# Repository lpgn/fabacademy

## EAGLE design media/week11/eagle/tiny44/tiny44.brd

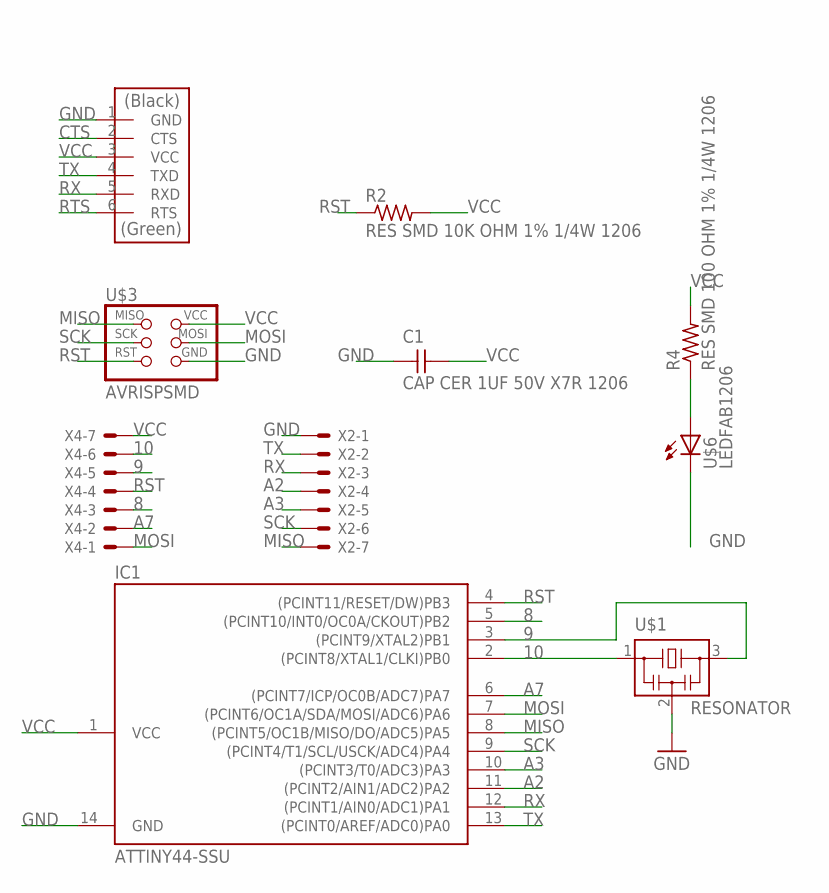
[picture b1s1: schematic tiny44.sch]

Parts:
C1: CAP CER 1UF 50V X7R 1206; C1206FAB
IC1: ATTINY44-SSU; SOIC14
R2: RES SMD 10K OHM 1% 1/4W 1206; R1206FAB
R4: RES SMD 100 OHM 1% 1/4W 1206; R1206FAB
U$1: RESONATOR; EFOBM; MPN AWSCR-20.00MTD-T
U$2: FTDI-SMD-HEADER; 1X06SMD
U$3: AVRISPSMD; 2X03SMD
U$6: LEDFAB1206; LED1206FAB
X2, X4: KK-156-7

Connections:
8: IC1.5 ((PCINT10/INT0/OC0A/CKOUT)PB2), X4.3
9: IC1.3 ((PCINT9/XTAL2)PB1), U$1.3, X4.5
10: IC1.2 ((PCINT8/XTAL1/CLKI)PB0), U$1.1, X4.6
A2: IC1.11 ((PCINT2/AIN1/ADC2)PA2), X2.4
A3: IC1.10 ((PCINT3/T0/ADC3)PA3), X2.5
A7: IC1.6 ((PCINT7/ICP/OC0B/ADC7)PA7), X4.2
CTS: U$2.2 (CTS)
GND: C1.1, IC1.14 (GND), U$1.2, U$2.1 (GND), U$3.6 (GND), U$6.2 (C), X2.1
MISO: IC1.8 ((PCINT5/OC1B/MISO/DO/ADC5)PA5), U$3.1 (MISO), X2.7
MOSI: IC1.7 ((PCINT6/OC1A/SDA/MOSI/ADC6)PA6), U$3.4 (MOSI), X4.1
PB2: R4.1, U$6.1 (A)
RST: IC1.4 ((PCINT11/RESET/DW)PB3), R2.1, U$3.5 (RST), X4.4
RTS: U$2.6 (RTS)
RX: IC1.12 ((PCINT1/AIN0/ADC1)PA1), U$2.5 (RXD), X2.3
SCK: IC1.9 ((PCINT4/T1/SCL/USCK/ADC4)PA4), U$3.3 (SCK), X2.6
TX: IC1.13 ((PCINT0/AREF/ADC0)PA0), U$2.4 (TXD), X2.2
VCC: C1.2, IC1.1 (VCC), R2.2, R4.2, U$2.3 (VCC), U$3.2 (VCC), X4.7

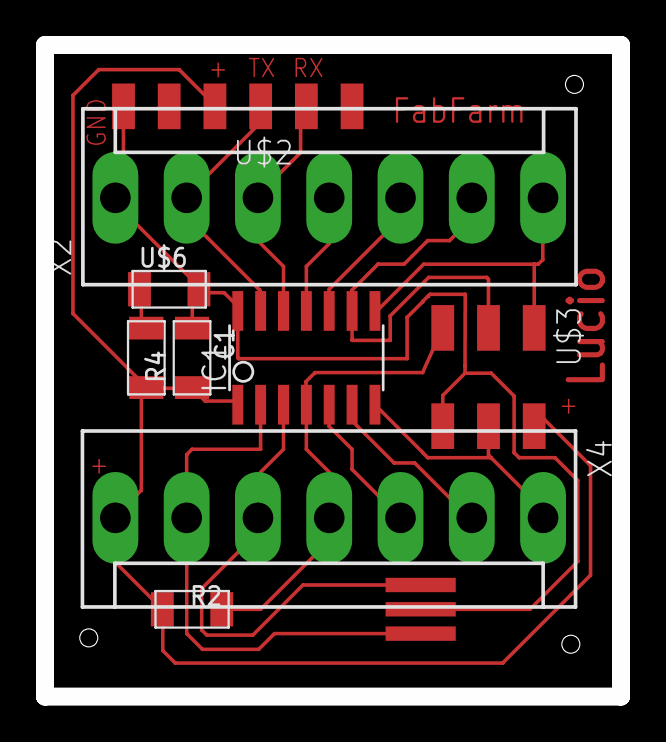
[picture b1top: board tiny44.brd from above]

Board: 2 copper layers, 32.0 x 36.2 mm, 10 parts (0 on the bottom side), 15 nets.

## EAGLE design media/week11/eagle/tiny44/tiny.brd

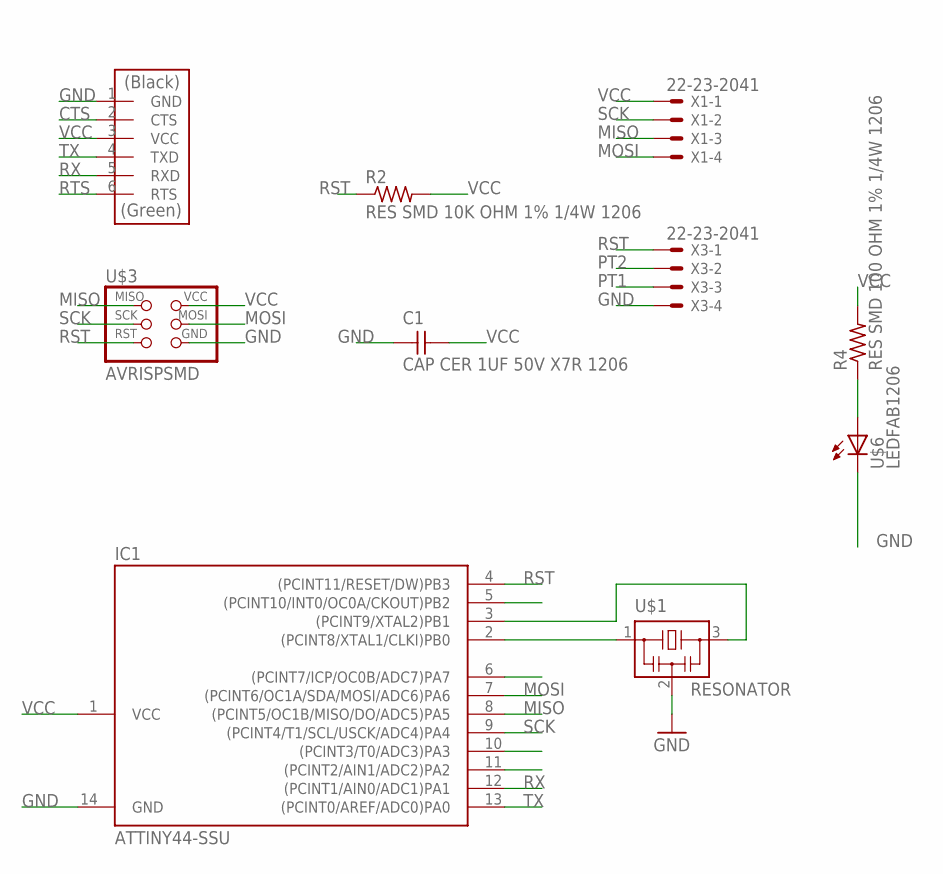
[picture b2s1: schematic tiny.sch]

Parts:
C1: CAP CER 1UF 50V X7R 1206; C1206FAB
IC1: ATTINY44-SSU; SOIC14
R2: RES SMD 10K OHM 1% 1/4W 1206; R1206FAB
R4: RES SMD 100 OHM 1% 1/4W 1206; R1206FAB
U$1: RESONATOR; EFOBM; MPN AWSCR-20.00MTD-T
U$2: FTDI-SMD-HEADER; 1X06SMD
U$3: AVRISPSMD; 2X03SMD
U$6: LEDFAB1206; LED1206FAB
X1, X3: 22-23-2041

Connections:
CTS: U$2.2 (CTS)
GND: C1.1, IC1.14 (GND), U$1.2, U$2.1 (GND), U$3.6 (GND), U$6.2 (C), X3.4
MISO: IC1.8 ((PCINT5/OC1B/MISO/DO/ADC5)PA5), U$3.1 (MISO), X1.3
MOSI: IC1.7 ((PCINT6/OC1A/SDA/MOSI/ADC6)PA6), U$3.4 (MOSI), X1.4
unnamed: IC1.3 ((PCINT9/XTAL2)PB1), U$1.3
unnamed: IC1.2 ((PCINT8/XTAL1/CLKI)PB0), U$1.1
PB2: R4.1, U$6.1 (A)
PT1: X3.3
PT2: X3.2
RST: IC1.4 ((PCINT11/RESET/DW)PB3), R2.1, U$3.5 (RST), X3.1
RTS: U$2.6 (RTS)
RX: IC1.12 ((PCINT1/AIN0/ADC1)PA1), U$2.5 (RXD)
SCK: IC1.9 ((PCINT4/T1/SCL/USCK/ADC4)PA4), U$3.3 (SCK), X1.2
TX: IC1.13 ((PCINT0/AREF/ADC0)PA0), U$2.4 (TXD)
VCC: C1.2, IC1.1 (VCC), R2.2, R4.2, U$2.3 (VCC), U$3.2 (VCC), X1.1

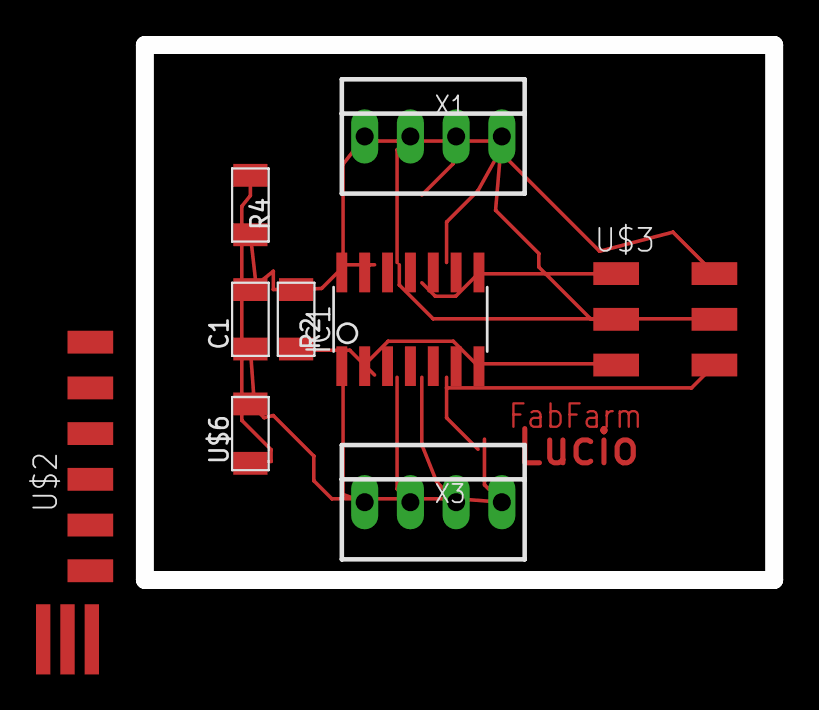
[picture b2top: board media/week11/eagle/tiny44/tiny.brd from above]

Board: 2 copper layers, 35.0 x 29.7 mm, 10 parts (0 on the bottom side), 11 nets.

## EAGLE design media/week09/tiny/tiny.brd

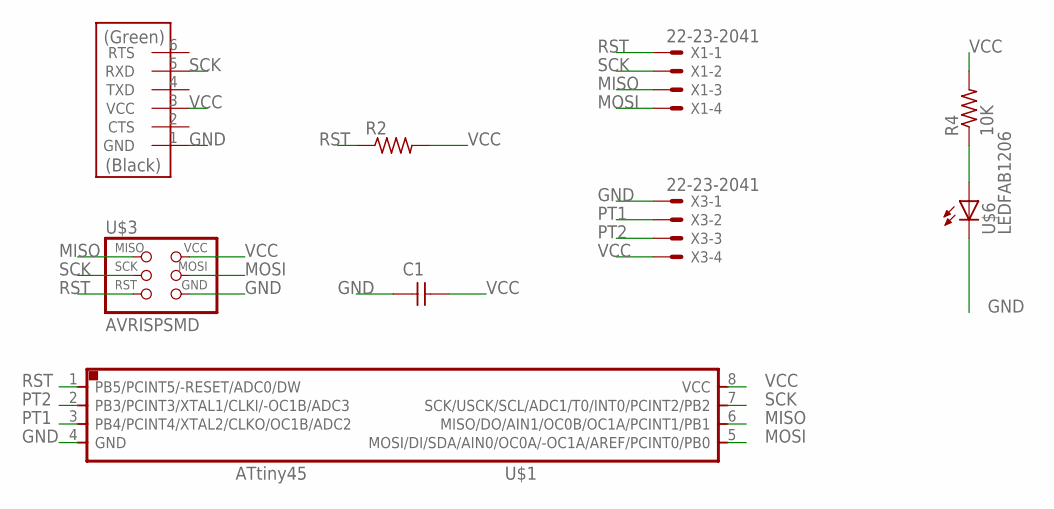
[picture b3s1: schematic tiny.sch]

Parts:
C1: CAP-UNPOLARIZEDFAB; C1206FAB
R2: RES-US1206FAB; R1206FAB
R4: 10K; R1206FAB
U$1: ATTINY45SI; SOIC8
U$3: AVRISPSMD; 2X03SMD
U$4: FTDI-SMD-HEADER; 1X06SMD
U$6: LEDFAB1206; LED1206FAB
X1, X3: 22-23-2041

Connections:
GND: C1.1, U$1.4 (GND), U$3.6 (GND), U$4.1 (GND), U$6.2 (C), X3.1
MISO: U$1.6 (MISO/DO/AIN1/OC0B/OC1A/PCINT1/PB1), U$3.1 (MISO), X1.3
MOSI: U$1.5 (MOSI/DI/SDA/AIN0/OC0A/-OC1A/AREF/PCINT0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), U$3.4 (MOSI), X1.4
PB2: R4.1, U$6.1 (A)
PT1: U$1.3 (PB4/PCINT4/XTAL2/CLKO/OC1B/ADC2), X3.2
PT2: U$1.2 (PB3/PCINT3/XTAL1/CLKI/-OC1B/ADC3), X3.3
RST: R2.1, U$1.1 (PB5/PCINT5/-RESET/ADC0/DW), U$3.5 (RST), X1.1
SCK: U$1.7 (SCK/USCK/SCL/ADC1/T0/INT0/PCINT2/PB2), U$3.3 (SCK), U$4.5 (RXD), X1.2
VCC: C1.2, R2.2, R4.2, U$1.8 (VCC), U$3.2 (VCC), U$4.3 (VCC), X3.4

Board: 2 copper layers, 9 parts (0 on the bottom side), 9 nets, no tracks yet.

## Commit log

2018-02-26 Add new file
2018-02-26 Initial commit after migration to new git repo
2018-02-27 Week 6 first part
2018-02-27 html was not saved before now it is
2018-02-28 week6
2018-02-28 small fix
2018-02-28 english language error correction
2018-03-06 updates for week 7
2020-02-01 adaptations to 2020
2020-02-10 week2 images and other changes
2020-02-10 spell check
2020-02-10 spell check2
2020-02-12 week3 media
2020-02-19 week4 media
2020-02-26 adding media for week5
2020-02-26 adding gcode
2020-02-26 adding video
2020-02-26 adding stl file
2020-02-26 adding another stl file
2020-02-26 yet anothert stl
2020-03-03 week5 details
2020-03-04 week5 added pic
2020-03-04 week5 text change
2020-03-04 week6 media
2020-03-11 week8 media
2020-04-01 week9 media
2020-04-02 video max hight added to css
2020-04-02 changing order of git commands
2020-04-02 signing Fab Academy Student Agreement
2020-04-17 week07 media
2020-04-17 typo
2020-04-21 week7
2020-04-22 week7 adding text
2020-05-04 week2 media insertion
2020-05-04 adding links and code on week08
2020-05-04 code
2020-05-06 adding content to final project and other stuff
2020-05-06 deleting stuff
2020-05-13 details on week 05 and 06
    details on week 05 and 06
2020-05-13 Update exercise05.html
    update exercise 05
2020-05-20 week12
2020-05-20 media12
2020-05-21 week12 and 09
2020-05-21 videofile
2020-05-21 datasheet
2020-05-21 boards and video
2020-05-21 video of water boiling
2020-05-21 another video
2020-05-21 update on embbebed programing week 8
2020-05-21 fixing broken links
2020-05-21 replacing video
2020-05-21 adding video and pics
2020-05-21 week12 and CAD CAM files
2020-05-23 partial week11
2020-05-25 week11 and start week16
2020-05-25 week11 final I think
2020-05-26 updating week 09 and 10
2020-05-26 adding text to week09
2020-05-26 commit updated pics
2020-05-27 comply with names of exercises instead of week number
2020-05-27 change
2020-05-27 comply exercise
2020-05-27 comply week names
2020-05-27 broken link fix
2020-05-28 update principles and practice
2020-05-28 update wildcard week
2020-05-28 fix link
2020-05-28 heroshot
2020-05-30 small changes in code and etc...
2020-05-31 student agreement and others
2020-05-31 more details in electronic production
2020-05-31 small changes :-)
2020-05-31 fix broken links
2020-05-31 added preparation of scanned model
2020-05-31 requested changes
2020-05-31 fix links
2020-06-01 inkscape stuff
2020-06-02 more detail on electronics week
2020-06-02 slicer settings in 3dscanning and printing
2020-06-03 various
2020-06-04 molding and casting
2020-06-04 molding and casting text
2020-06-07 update final project, add more documentation to molding and casting and fix many typo and others
2020-06-07 forgoten file updates from last commit
2020-06-08 added links to electronic programing
2020-06-09 project update and errata
2020-06-09 video
2020-06-12 code change function really works now
2020-06-14 13062020 updates
2020-06-15 daily update
2020-06-15 today update
2020-06-18 interface week
2020-06-22 images
2020-06-25 rename program
2020-06-25 programming
2020-07-02 updates network
2020-07-05 network partial
2020-07-06 network images
2020-07-12 updates on networking
2020-07-22 fianlproject
2020-10-17 deleting old stuff
2020-10-28 computercontroledcutting
2023-12-27 test
2025-01-29 updates for final project
2025-02-15 proof reading
2025-02-15 improve
2025-02-15 seo changes
